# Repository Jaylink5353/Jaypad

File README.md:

My Hackpad!! Thanks Hack Club and Highway to Hardware!!!!

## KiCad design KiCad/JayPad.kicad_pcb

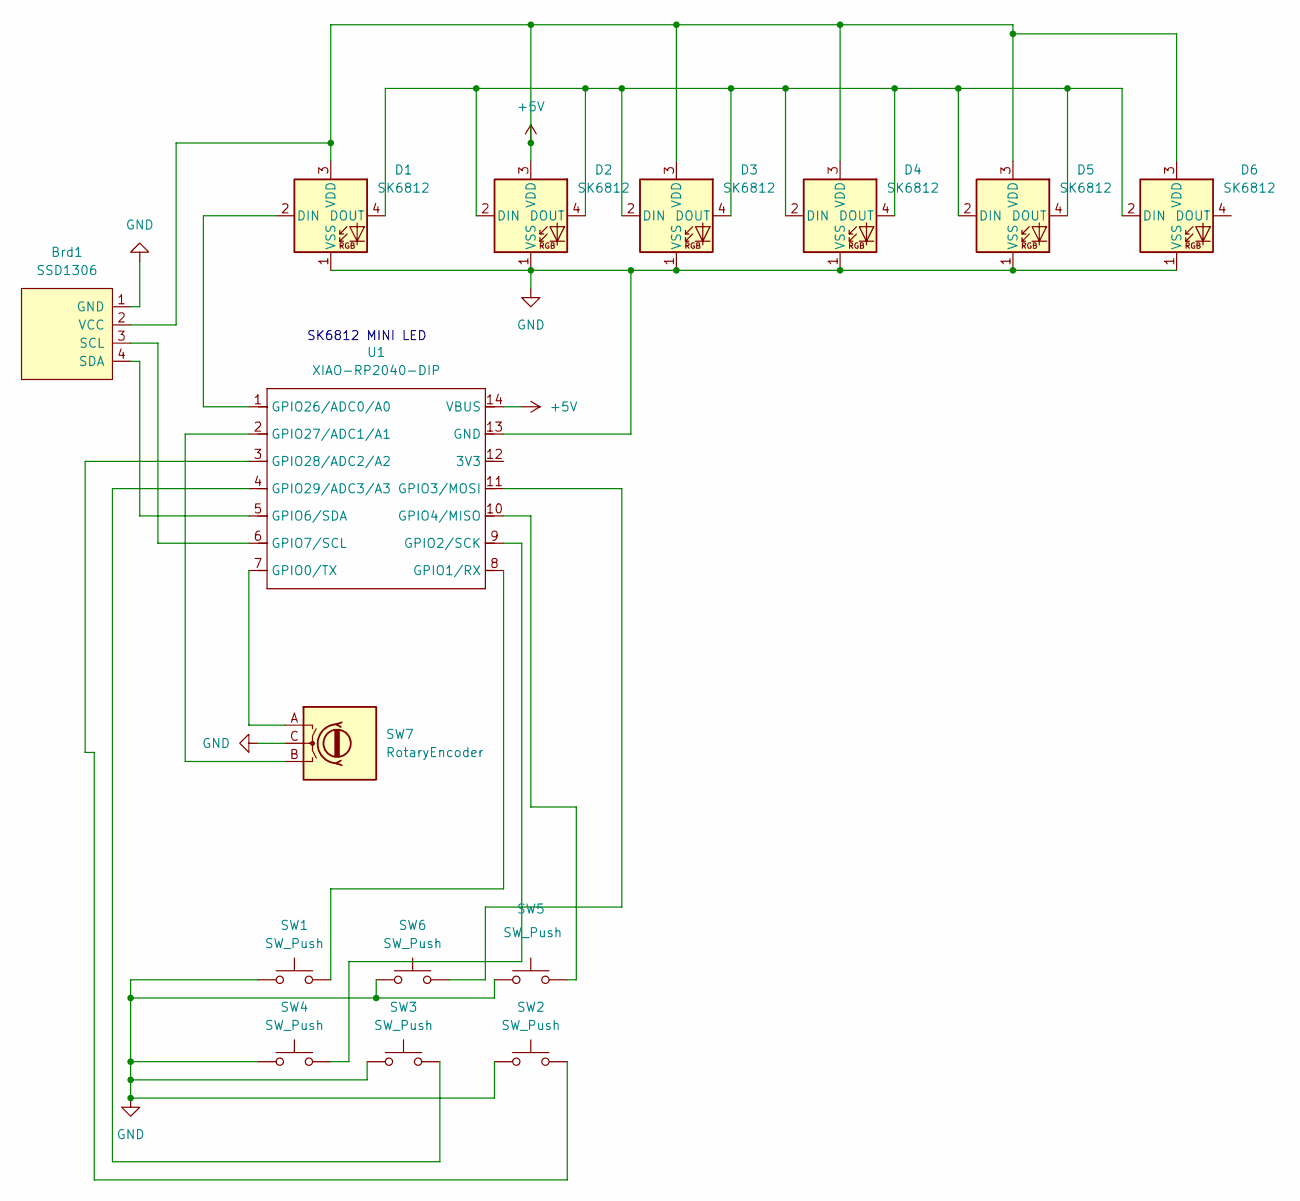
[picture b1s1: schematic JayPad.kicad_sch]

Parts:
Brd1: SSD1306; SSD1306-0.91-OLED-4pin-128x32
D1, D2, D3, D4, D5, D6: SK6812; LED_SK6812_PLCC4_5.0x5.0mm_P3.2mm
SW1, SW2, SW3, SW4, SW5, SW6: SW_Push; SW_Cherry_MX_1.00u_PCB
SW7: RotaryEncoder; RotaryEncoder_Alps_EC11E-Switch_Vertical_H20mm
U1: XIAO-RP2040-DIP

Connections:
+5V: Brd1.2 (VCC), D1.3 (VDD), D2.3 (VDD), D3.3 (VDD), D4.3 (VDD), D5.3 (VDD), D6.3 (VDD), U1.14 (VBUS)
GND: Brd1.1 (GND), D1.1 (VSS), D2.1 (VSS), D3.1 (VSS), D4.1 (VSS), D5.1 (VSS), D6.1 (VSS), SW1.1, SW2.1, SW3.1, SW4.1, SW5.1, SW6.1, SW7.C, U1.13 (GND)
unnamed: Brd1.3 (SCL), U1.6 (GPIO7/SCL)
unnamed: Brd1.4 (SDA), U1.5 (GPIO6/SDA)
unnamed: D1.2 (DIN), U1.1 (GPIO26/ADC0/A0)
unnamed: D1.4 (DOUT), D2.2 (DIN), D2.4 (DOUT), D3.2 (DIN), D3.4 (DOUT), D4.2 (DIN), D4.4 (DOUT), D5.2 (DIN), D5.4 (DOUT), D6.2 (DIN)
unnamed: SW7.A, U1.7 (GPIO0/TX)
unnamed: SW1.2, U1.8 (GPIO1/RX)
unnamed: SW4.2, U1.9 (GPIO2/SCK)
unnamed: SW6.2, U1.11 (GPIO3/MOSI)
unnamed: SW5.2, U1.10 (GPIO4/MISO)
unnamed: SW7.B, U1.2 (GPIO27/ADC1/A1)
unnamed: SW2.2, U1.3 (GPIO28/ADC2/A2)
unnamed: SW3.2, U1.4 (GPIO29/ADC3/A3)

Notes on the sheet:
SK6812 MINI LED

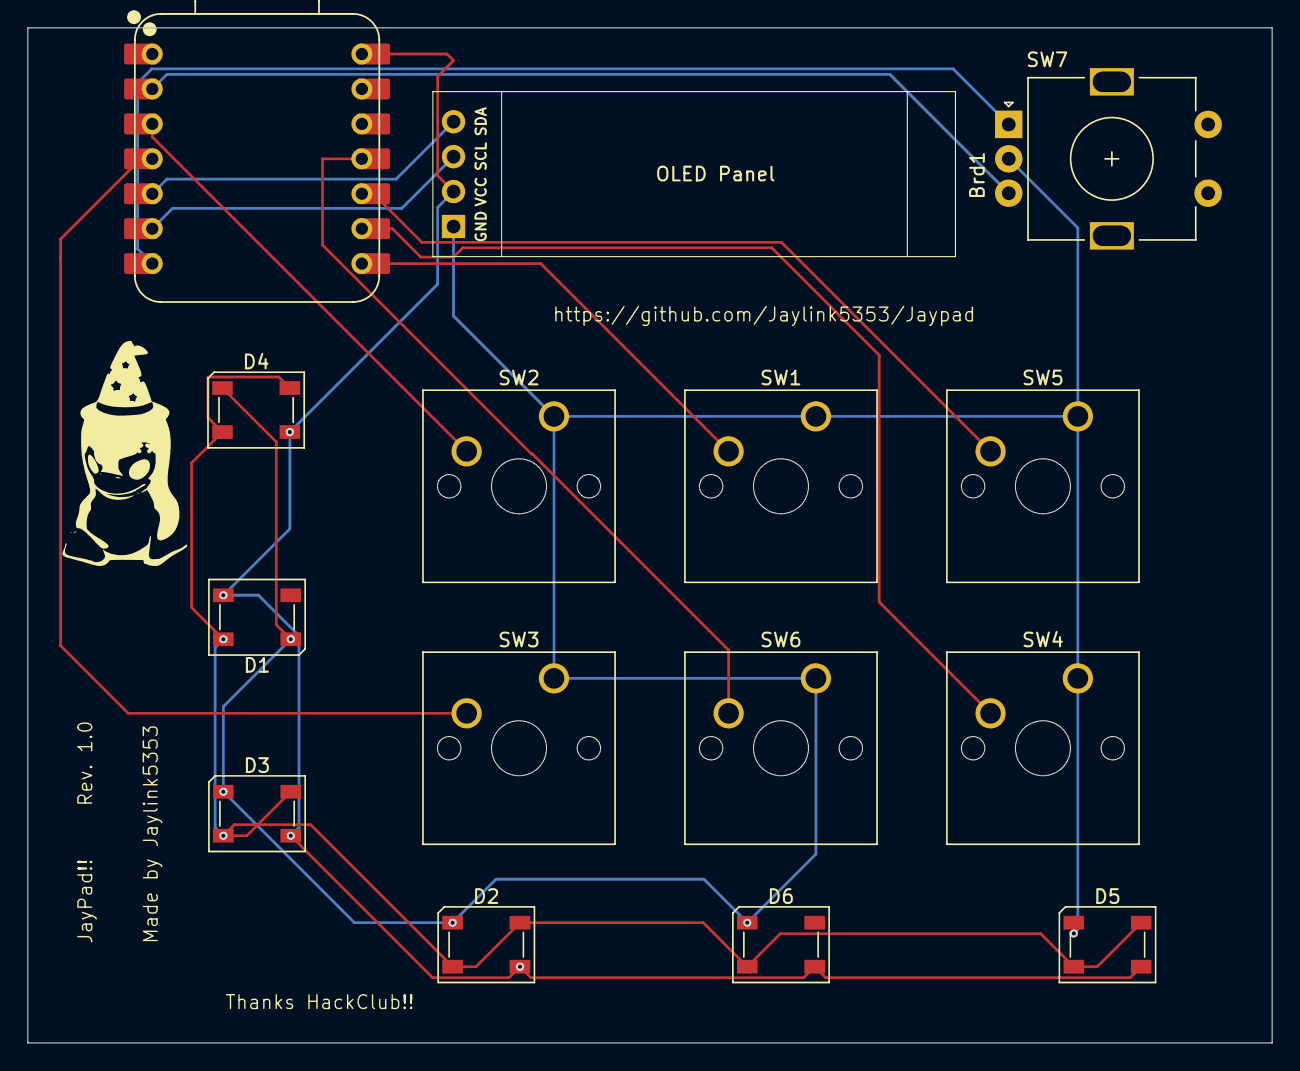
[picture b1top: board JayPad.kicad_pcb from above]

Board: 2 copper layers, 90.5 x 73.8 mm, 15 parts (0 on the bottom side), 14 nets.

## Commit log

2025-06-17 Init, Added PCB Files so far
2025-06-18 Finished Routing PCB!
2025-06-18 Finished PCB!!
